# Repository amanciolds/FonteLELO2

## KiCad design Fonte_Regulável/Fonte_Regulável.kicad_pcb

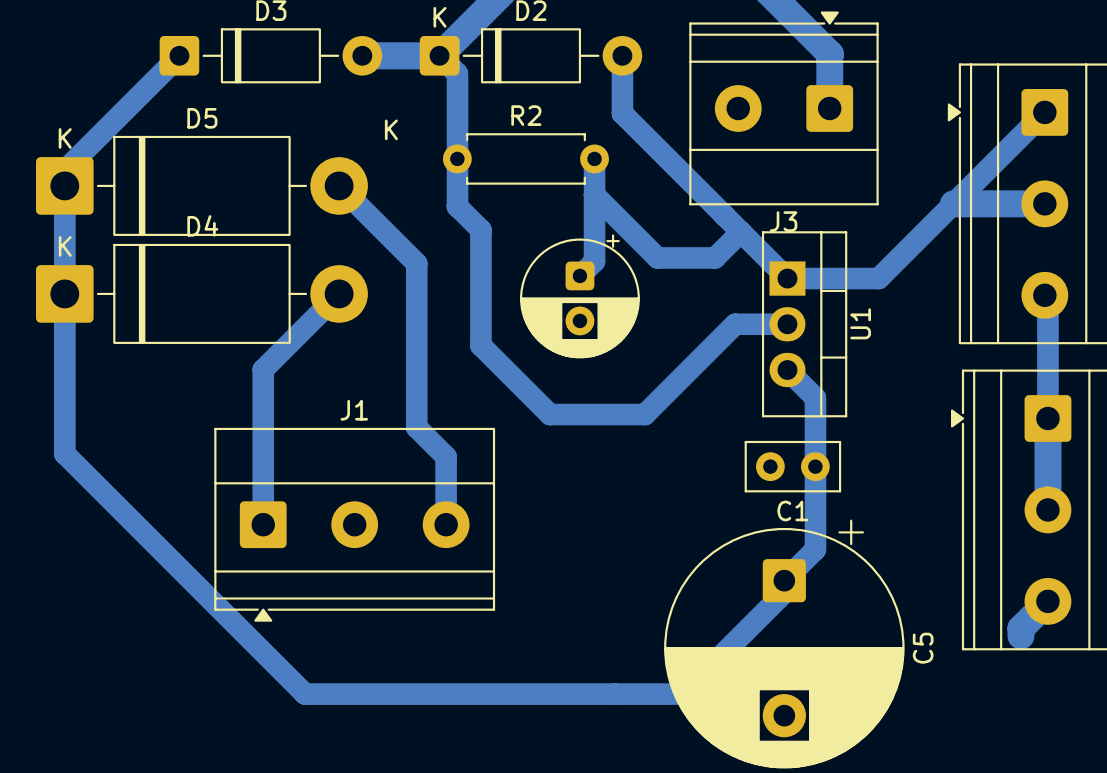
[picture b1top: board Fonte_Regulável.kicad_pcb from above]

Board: 2 copper layers, 13 parts (0 on the bottom side), 7 nets.

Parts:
C1: 0.1 uF; C_Disc_D5.0mm_W2.5mm_P2.50mm
C3: 10uF; CP_Radial_D6.3mm_P2.50mm
C5: 2200 uF; CP_Radial_D13.0mm_P7.50mm
D2, D3: 1N4002; D_DO-41_SOD81_P10.16mm_Horizontal
D4, D5: 1N5408; D_DO-201AD_P15.24mm_Horizontal
J1: Screw_Terminal_01x02; TerminalBlock_Phoenix_MKDS-1,5-3-5.08_1x03_P5.08mm_Horizont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
J2, J4: Potenciometro; TerminalBlock_Phoenix_MKDS-1,5-3-5.08_1x03_P5.08mm_Horizont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
J3: Screw_Terminal_01x02; TerminalBlock_Phoenix_MKDS-1,5-2-5.08_1x02_P5.08mm_Horizont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
R2: 240; R_Axial_DIN0207_L6.3mm_D2.5mm_P7.62mm_Horizontal
U1: LM317_SOT-223; TO-220-3_Vertical

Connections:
Earth: C1.2, C3.2, C5.2, J1.2, J3.2, J4.3
unnamed: C3.1, D2.2 (A), J2.1, J2.2, R2.2, U1.1 (ADJ)
unnamed: D2.1 (K), D3.2 (A), J3.1, R2.1, U1.2 (VO)
unnamed: C1.1, C5.1, D3.1 (K), D4.1 (K), D5.1 (K), U1.3 (VI)
unnamed: D4.2 (A), J1.1
unnamed: D5.2 (A), J1.3
unnamed: J2.3, J4.1, J4.2
